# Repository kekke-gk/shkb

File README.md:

# SHKB

SHKB is a split keyboard with B and 6 keys on both sides.
The keyboard layout is based on [HHKB](https://happyhackingkb.com).

## Photos

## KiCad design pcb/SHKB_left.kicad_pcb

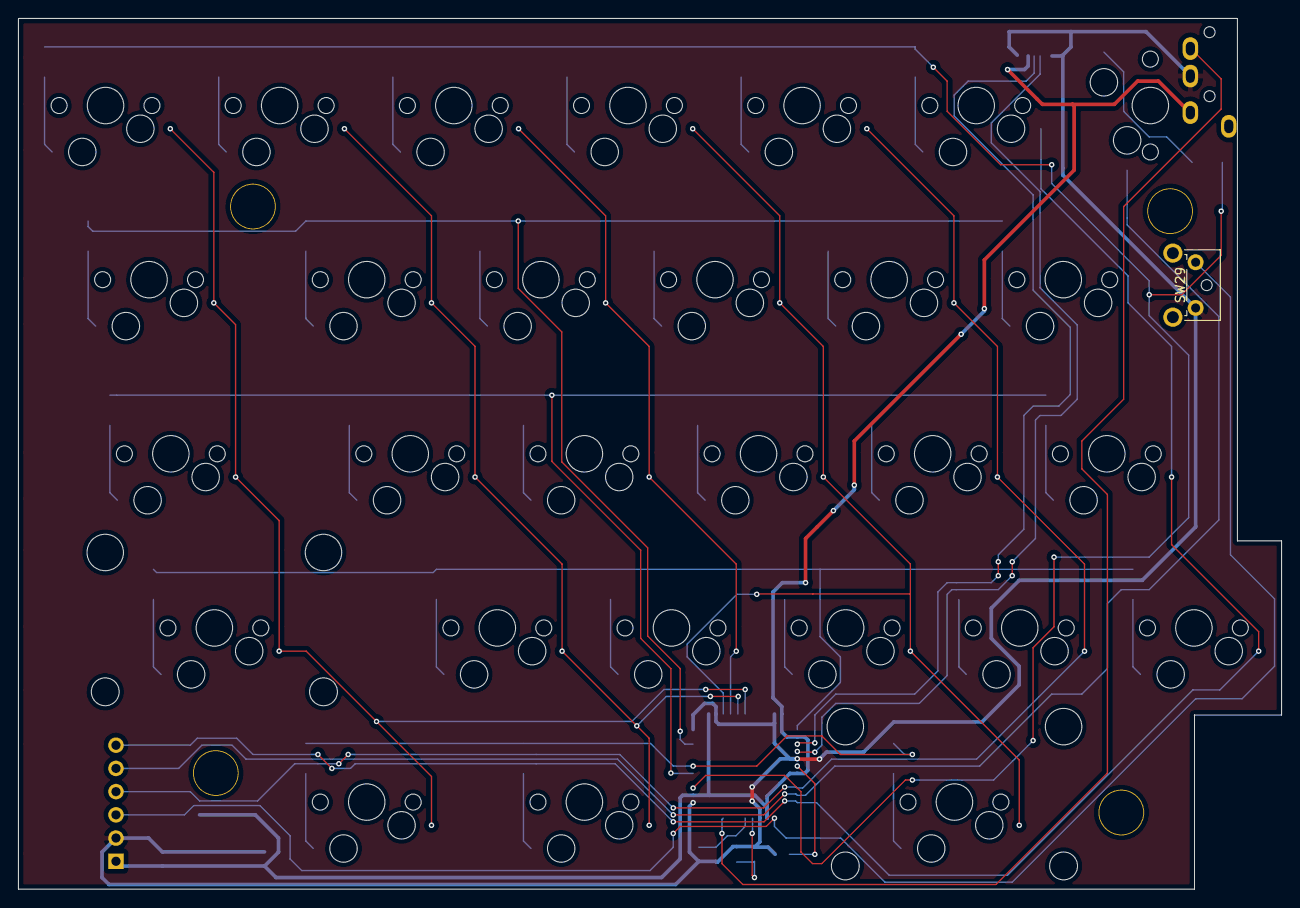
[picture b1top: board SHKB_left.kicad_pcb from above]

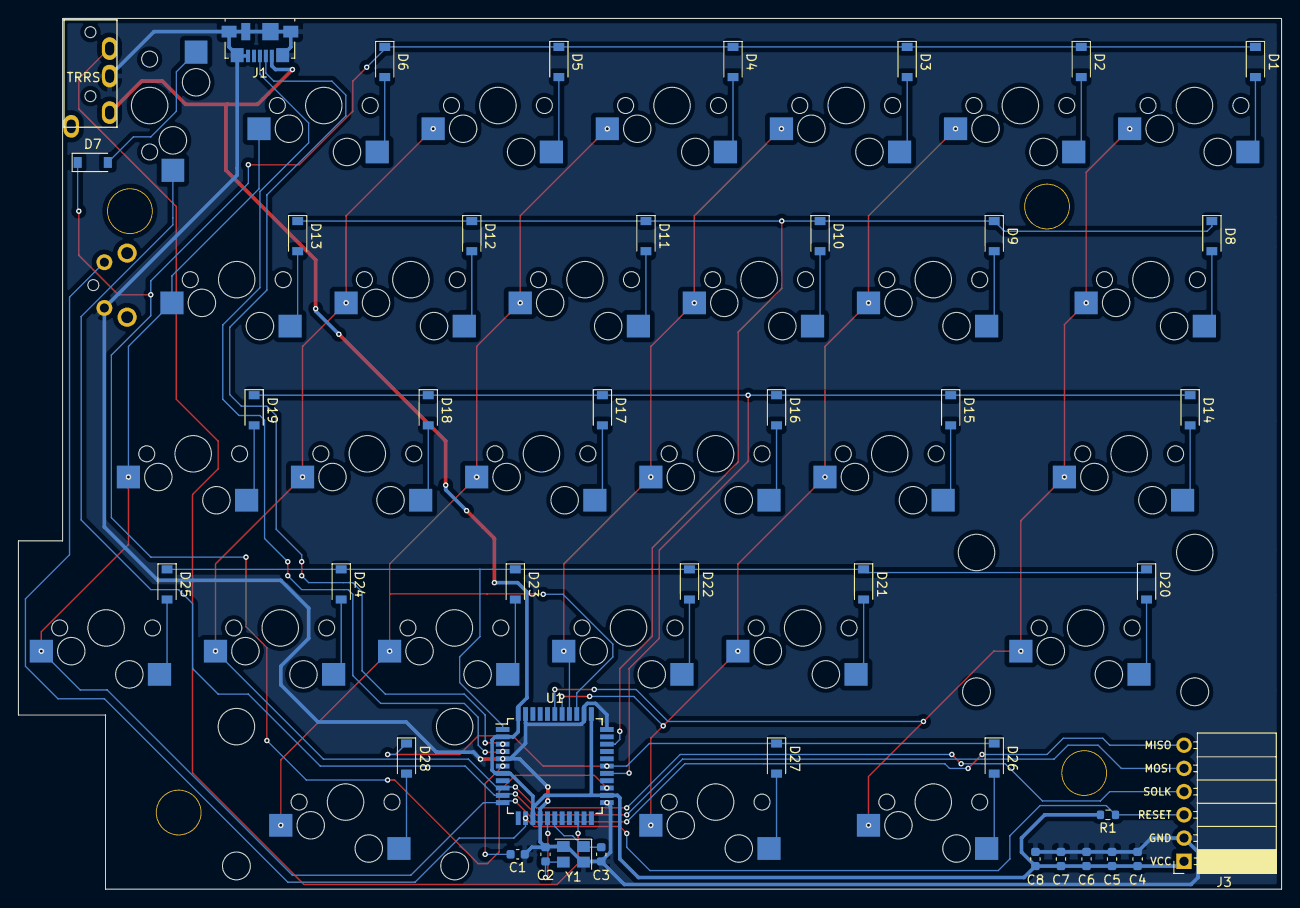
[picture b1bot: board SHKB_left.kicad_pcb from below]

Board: 2 copper layers, 138.2 x 95.2 mm, 75 parts (42 on the bottom side), 49 nets.

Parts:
C1: 1uF; C_0603_1608Metric
C2, C3: 22pF; C_0603_1608Metric
C4, C5, C6, C7: 100nF; C_0603_1608Metric
C8: 4.7uF; C_0603_1608Metric
D1, D2, D3, D4, D5, D6, D7, D8, D9, D10, D11, D12, D13, D14, D15, D16, D17, D18, D19, D20, D21, D22, D23, D24, D25, D26, D27, D28: D; D_SOD-123
J1: USB_B_Micro; USB_Micro-B_Molex_47346-0001
J2: MJ-4PP-9; MJ-4PP-9_1side
J3: Conn_01x06_Female; PinSocket_1x06_P2.54mm_Horizontal
R1: 10k; R_0603_1608Metric
Ref**: Val**; HOLE
Ref**#2, Ref**#3, Ref**#4: Val**; HOLE
SW1, SW2, SW3, SW4, SW5, SW6, SW7, SW9, SW10, SW11, SW12, SW13, SW15, SW16, SW17, SW18, SW19, SW21, SW22, SW23, SW24, SW25, SW26: SW_PUSH; MXOnly-1U-Hotswap
SW8, SW27: SW_PUSH; MXOnly-1.5U-Hotswap
SW14: SW_PUSH; MXOnly-1.75U-Hotswap
SW20: SW_PUSH; MXOnly-2.25U-Hotswap
SW28: SW_PUSH; MXOnly-2.75U-Hotswap
SW29: SW_PUSH; SW_Tactile_SPST_Angled_MJTP1117
U1: ATmega32U4-AU; TQFP-44_10x10mm_P0.8mm
Y1: Crystal_GND24; Crystal_SMD_3225-4Pin_3.2x2.5mm

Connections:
D+: J1.3, U1.4
D-: J1.2, U1.3
GND: C1.1, C2.1, C3.1, C4.2, C5.2, C6.2, C7.2, C8.2, J1.5, J1.6, J2.C, J3.2, SW29.2, U1.5, U1.15, U1.23, U1.33, U1.35, U1.43, Y1.2, Y1.4
MISO: J3.6, SW6.1, SW13.1, SW19.1, SW25.1, U1.11
MOSI: J3.5, SW7.1, U1.10
unnamed: C1.2, U1.6
unnamed: D1.2, SW1.2
unnamed: D2.2, SW2.2
unnamed: D3.2, SW3.2
unnamed: D4.2, SW4.2
unnamed: D5.2, SW5.2
unnamed: D6.2, SW6.2
unnamed: D7.2, SW7.2
unnamed: D8.2, SW8.2
unnamed: D9.2, SW9.2
unnamed: D10.2, SW10.2
unnamed: D11.2, SW11.2
unnamed: D12.2, SW12.2
unnamed: D13.2, SW13.2
unnamed: D14.2, SW14.2
unnamed: D15.2, SW15.2
unnamed: D16.2, SW16.2
unnamed: D17.2, SW17.2
unnamed: D18.2, SW18.2
unnamed: D19.2, SW19.2
unnamed: D20.2, SW20.2
unnamed: D21.2, SW21.2
unnamed: D22.2, SW22.2
unnamed: D23.2, SW23.2
unnamed: D24.2, SW24.2
unnamed: D25.2, SW25.2
unnamed: D26.2, SW26.2
unnamed: D27.2, SW27.2
unnamed: D28.2, SW28.2
RESET: J3.3, R1.1, SW29.1, U1.13
SOLK: J3.4, SW5.1, SW12.1, SW18.1, SW24.1, U1.9
VCC: C4.1, C5.1, C6.1, C7.1, C8.1, J1.1, J2.D, J3.1, R1.2, U1.2, U1.7, U1.14, U1.24, U1.34, U1.44
XTAL1: C3.2, U1.17, Y1.1
XTAL2: C2.2, U1.16, Y1.3
col0: SW1.1, SW8.1, SW14.1, SW20.1, SW26.1, U1.39
col1: SW2.1, SW9.1, SW15.1, SW21.1, SW27.1, U1.38
col2: SW3.1, SW10.1, SW16.1, SW22.1, U1.37
col3: SW4.1, SW11.1, SW17.1, SW23.1, SW28.1, U1.36
data: J2.B, U1.20
row0: D1.1, D2.1, D3.1, D4.1, D5.1, D6.1, D7.1, U1.25
row1: D8.1, D9.1, D10.1, D11.1, D12.1, D13.1, U1.31
row2: D14.1, D15.1, D16.1, D17.1, D18.1, D19.1, U1.27
row3: D20.1, D21.1, D22.1, D23.1, D24.1, D25.1, U1.1
row4: D26.1, D27.1, D28.1, U1.28

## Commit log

2022-09-10 Add pcb
2022-09-10 Add plates
2022-09-14 Modify README
